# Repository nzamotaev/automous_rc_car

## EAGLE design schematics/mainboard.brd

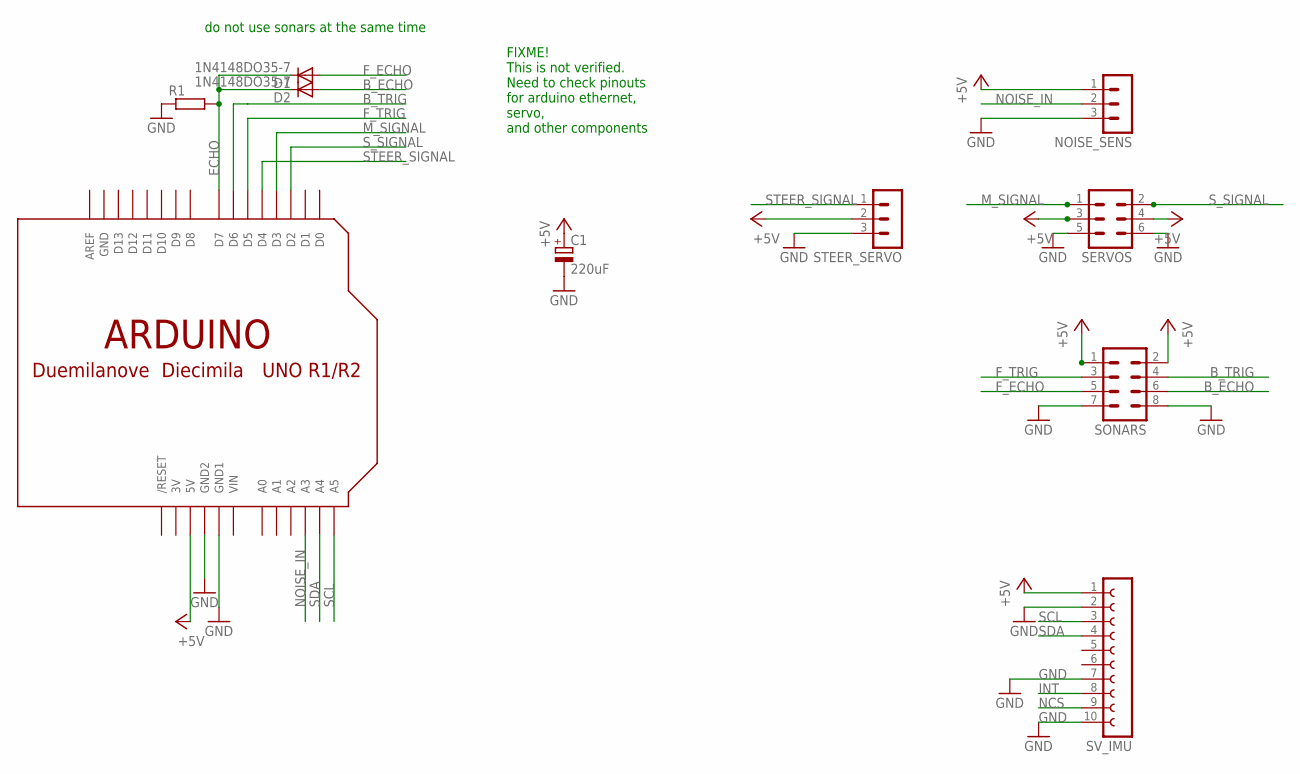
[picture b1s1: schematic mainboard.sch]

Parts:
C1: 220uF; E5-8,5
D1, D2: 1N4148DO35-7; DO35-7
NOISE_SENS: MA03-1
R1: R-EU_0204/2V; 0204V
SERVOS: MA03-2
SONARS: MA04-2
STEER_SERVO: MA03-1
SV_IMU: FE10-1; FE10
U$1: ARDUINOUNO; ARDUINO

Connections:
3V: U$1.3V
+5V: C1.+, NOISE_SENS.1, SERVOS.3, SERVOS.4, SONARS.1, SONARS.2, STEER_SERVO.2, SV_IMU.1, U$1.5V
B_ECHO: D2.A, SONARS.6
B_TRIG: SONARS.4, U$1.D6
ECHO: D1.C, D2.C, R1.2, U$1.D7
F_ECHO: D1.A, SONARS.5
F_TRIG: SONARS.3, U$1.D5
GND: C1.-, NOISE_SENS.3, R1.1, SERVOS.5, SERVOS.6, SONARS.7, SONARS.8, STEER_SERVO.3, SV_IMU.2, SV_IMU.7, SV_IMU.10, U$1.GND, U$1.GND1, U$1.GND2
INT: SV_IMU.8
M_SIGNAL: SERVOS.1, U$1.D3
NCS: SV_IMU.9
NOISE_IN: NOISE_SENS.2, U$1.A3
SCL: SV_IMU.3, U$1.A5
SDA: SV_IMU.4, U$1.A4
STEER_SIGNAL: STEER_SERVO.1, U$1.D4
S_SIGNAL: SERVOS.2, U$1.D2
VIN: U$1.VIN

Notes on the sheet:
FIXME! This is not verified. Need to check pinouts for arduino ethernet, servo, and other components
do not use sonars at the same time

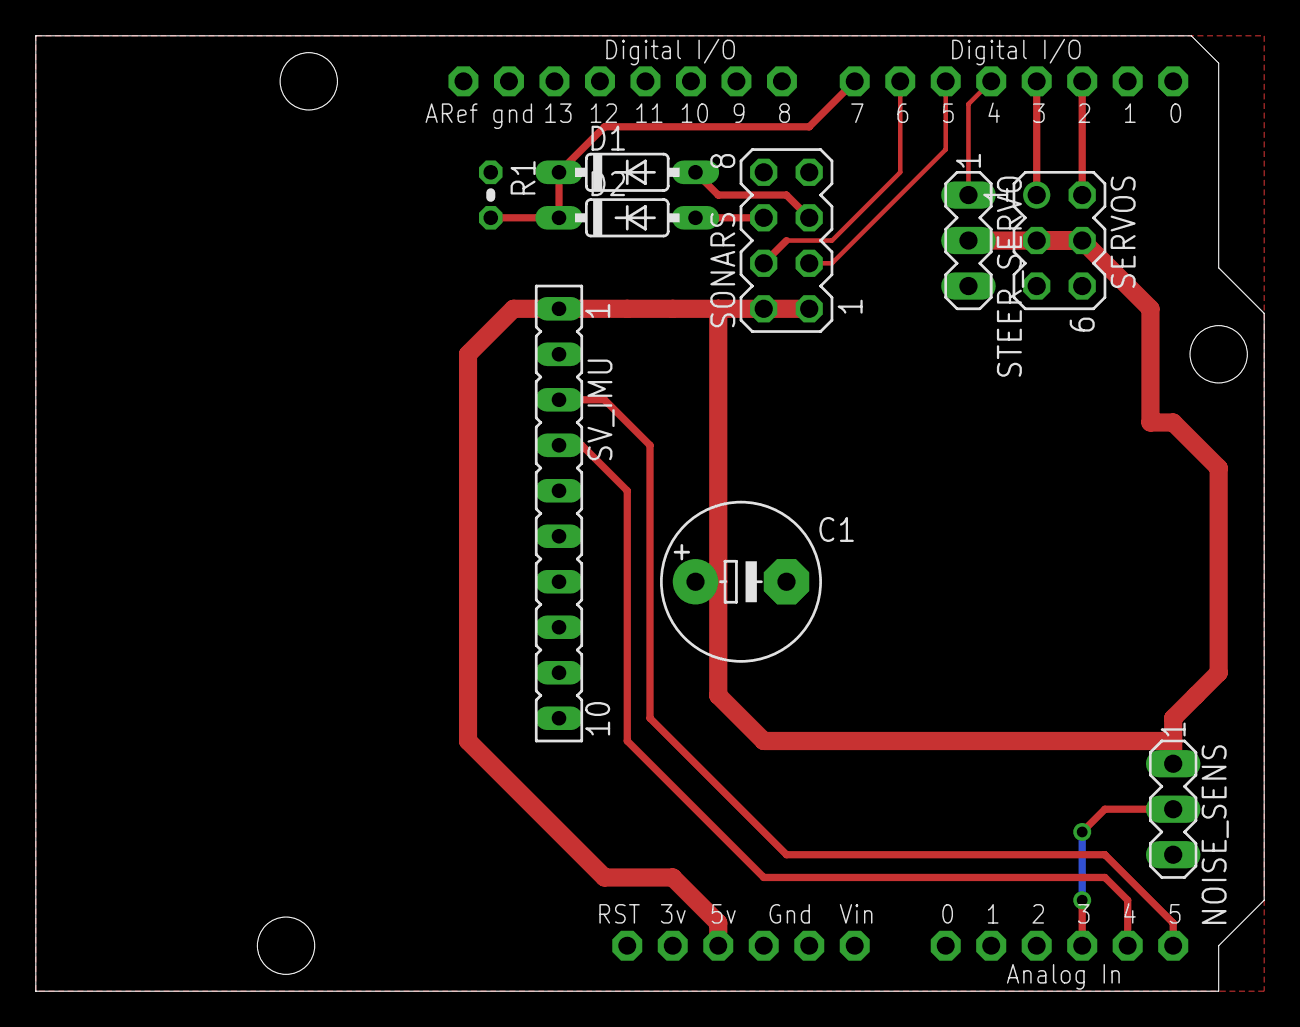
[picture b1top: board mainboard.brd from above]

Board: 2 copper layers, 68.6 x 53.3 mm, 10 parts (0 on the bottom side), 13 nets.

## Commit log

2017-08-29 Added initial version if schematics and shield
2017-08-29 Added placeholders for sensor tests
2017-08-29 Added sonar test sketch
2017-08-30 Changed schematics and pcb - new connectors, new arduino pins
2017-09-01 Updated schematics for 2 sonars. Added sonar test. Added makefiles
2017-09-01 Added sonar + servo test. Current issue - servo affects sonar (by sound?)
2017-09-01 Added steering servo motor test. Added blank template for the IMU test
    Steering servo causes reboot. Need to check further, with proper power supply (USB cable is not proper)
2017-09-05 Added power smoothing capacitor
2017-09-06 Added better visualisation
2017-09-13 Renamed PCB files
2017-09-13 Switched to 115200 in all scripts.
    Added IMU test.
    Added keyboard control to motor control.
    Swapped sonars for sonar servo test.
2017-09-13 Added main firmware code. Now can't really fit it into the flash.
2017-10-02 Added softpwm and PID libraries
2017-10-04 Switched to real servo
2017-10-04 Switched to proper servo. Updated PCB. Did not update for new IMU
2017-10-17 Added protothreads library
2017-10-17 Updated motor test. Added testing for sonars and auto stop. Added steering with servo along with turning of sonar
2017-11-29 Added initial version of qt control application
